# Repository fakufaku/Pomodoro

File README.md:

Pomodoro
========

A custom built timer for the [pomodoro technique](http://pomodorotechnique.com/).

Use it
------

1. One click starts a 25 minutes _work_ counter. Five yellow LED indicates how
  many slices of five minutes are left. There is a discrete beep when the timer
  expires. The LED then flashes to remind you to go into _rest_ mode.
2. A second click starts a 5 minutes _rest_ counter. A **red** LED is turned on.
  There is a discrete beep when it expires. Then the timer turns off.
3. If you wish the turn the timer off during _rest_ mode, click a third time the button.

Build it
--------

### Bill Of Material

* 1x ATtiny85
* 5x LED yellow, SMD 0805
* 1x LED red, SMD 0805
* 3x 22 Ohm Resistor, SMD 0805
* 2x 1K Ohm Resistor, SMD 0805
* 1x NPN BJT transistor, SOT-23 (BC846CMTF)
* 1x 1mH Inductor, SMD 1007
* 1x Buzzer, SMD [mouser](http://www.mouser.com/ProductDetail/Kobitone/254-PB501-ROX/?qs=%2fha2pyFaduio21Wb3%2fEgDw7Itv2u2RCUk%252bCSGDldQmgXvX6wRiKaqw%3d%3d)
* 1x CR2032 coin cell holder, SMD [mouser](http://www.mouser.com/ProductDetail/Linx-Technologies/BAT-HLD-001/?qs=sGAEpiMZZMupuRtfu7GC%252bdEIlVvqTbq%252bJLMEoC1V420%3d)
* 1x Tactile switch, SMD EVQ-Q2 [mouser](http://www.mouser.com/ProductDetail/Panasonic/EVQ-Q2K03W/?qs=sGAEpiMZZMsgGjVA3toVBA4puZS2llK5hCEf4xZ%2f9rI%3d)

### Schematic

### Etch the PCB

The PCB can be etched using the [mask](Pomodoro_mask.eps) provided in EPS format.
Here is a picture of the layout.

### Firmware

The firmware is in the `firmware` folder. It can be uploaded using avrdude and
a [usbtiny-isp](https://www.sparkfun.com/products/9825), for example. The idea is
to press a six-pin header againt the PCB directly when programing. Some spring-loaded
pins would be ideal for the job. The square pad is pad number one of a six-pin ISP
header.

To compile and upload (assuming you have avr-gcc and avrdude installed), type the
following in a terminal.

    make avrdude

The Code
--------

My goal was to use explore the possibilities of the ATtiny85 microcontroller. We use it here
as a timer that first counts 25 minutes (work time) and emit a signal. Then, we can start a second
counter for 5 minutes (rest time). Here is what we use.

* A tactile switch connected to the _INT0_ of the avr as the sole user input. We use it
  to turn the counter off and switch between different modes.
* A buzzer to give a discrete signal when the timer expires. The buzzer is driven
    by _TIMER0_ in PWM mode at 4 kHz, 50% duty cycle.
* As many LEDs as possible to indicate the progress of the timer. By default,
    the ATtiny85 has 5 GPIO pins (we could add an extra one, but would lose ISP).
    We have thus 3 GPIO remaining.   
    We assign all of them to LEDs and using
    [charlieplexing](https://en.wikipedia.org/wiki/Charlieplexing), it is
    possible to drive 6 LEDs using only 3 pins. We choose 5 yellow, for every 5
    minutes slice of the first timer, and a single red one, for the _rest time_
    of the second timer.

The code is completely interrupt driven. _TIMER1_ and its overflow interrupt
are used to keep track of time during each state. The tactile switch triggers
an interrupt to wake up the avr, or switch between states. The [finite state
machine](https://en.wikipedia.org/wiki/Finite-state_machine) looks like this.
Blue arrows are state switching triggered by a push on the button. Red arrows
are switching caused by the timer expiration.

The _main_ states are black circles. The grey circles are the transition states.
It was important to add the `BACKOFF` state to debounce the tactile button because it triggered multiple interrupts.

License
-------

2014 (c) Robin Scheibler aka FakuFaku

    "THE BEER-WARE LICENSE" (Revision 42):
    <fakufaku@gmail.com> wrote this file. As long as you retain this notice you
    can do whatever you want with this stuff. If we meet some day, and you think
    this stuff is worth it, you can buy me a beer in return -- Robin Scheibler

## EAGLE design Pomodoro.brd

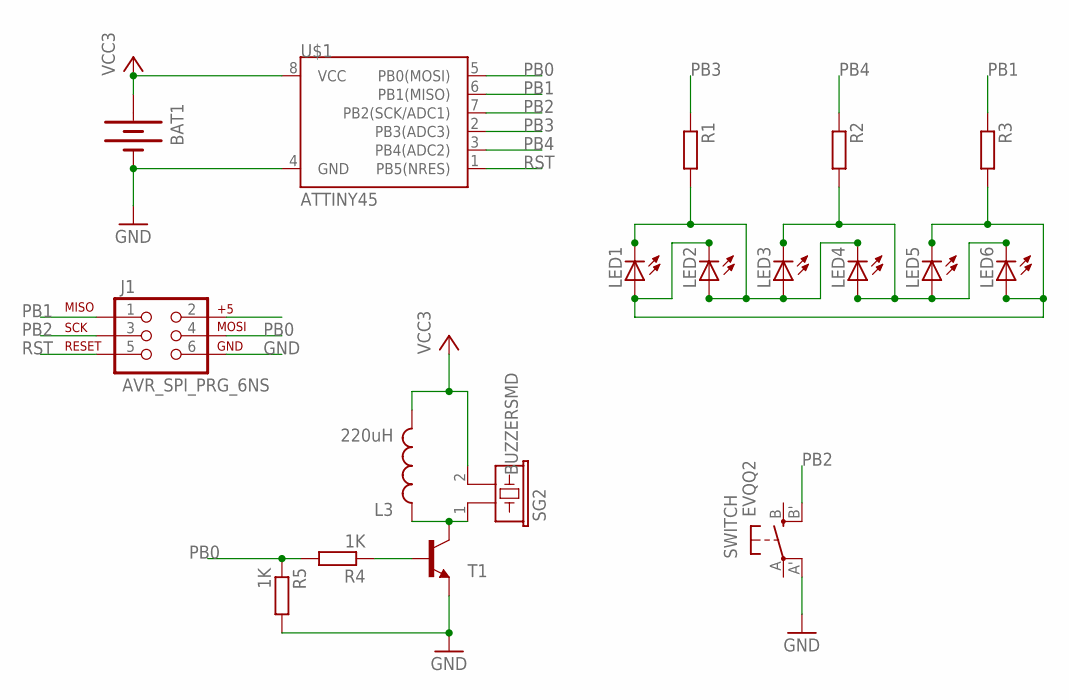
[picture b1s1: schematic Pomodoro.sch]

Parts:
BAT1: BATTERY20SMD; BATTCON_20MM
J1: AVR_SPI_PRG_6NS; 2X3-NS
L3: 220uH; 1007
LED1, LED2, LED3, LED4, LED5, LED6: LEDCHIPLED_0805; CHIPLED_0805
R1, R2, R3: R-EU_R0805; R0805
R4, R5: 1K; R0805
SG2: BUZZERSMD; KOBITONE-254-PB501-ROX
SWITCH: EVQQ2; EVQ-Q2
T1: BC849-NPN-SOT23-BEC; SOT23-BEC
U$1: ATTINY45; SO08-EIAJ

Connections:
GND: BAT1.2 (-), J1.6, R5.2, SWITCH.A' (P1), T1.E, U$1.4 (GND)
unnamed: R4.1, T1.B
unnamed: LED1.C, LED2.A, LED3.A, LED4.C, R1.2
unnamed: L3.1, SG2.1, T1.C
unnamed: LED3.C, LED4.A, LED5.A, LED6.C, R2.2
unnamed: LED1.A, LED2.C, LED5.C, LED6.A, R3.2
PB0: J1.4, R4.2, R5.1, U$1.5 (PB0(MOSI))
PB1: J1.1, R3.1, U$1.6 (PB1(MISO))
PB2: J1.3, SWITCH.B' (S1), U$1.7 (PB2(SCK/ADC1))
PB3: R1.1, U$1.2 (PB3(ADC3))
PB4: R2.1, U$1.3 (PB4(ADC2))
RST: J1.5, U$1.1 (PB5(NRES))
VCC3: BAT1.1 (+), BAT1.3 (+), L3.2, SG2.2, U$1.8 (VCC)

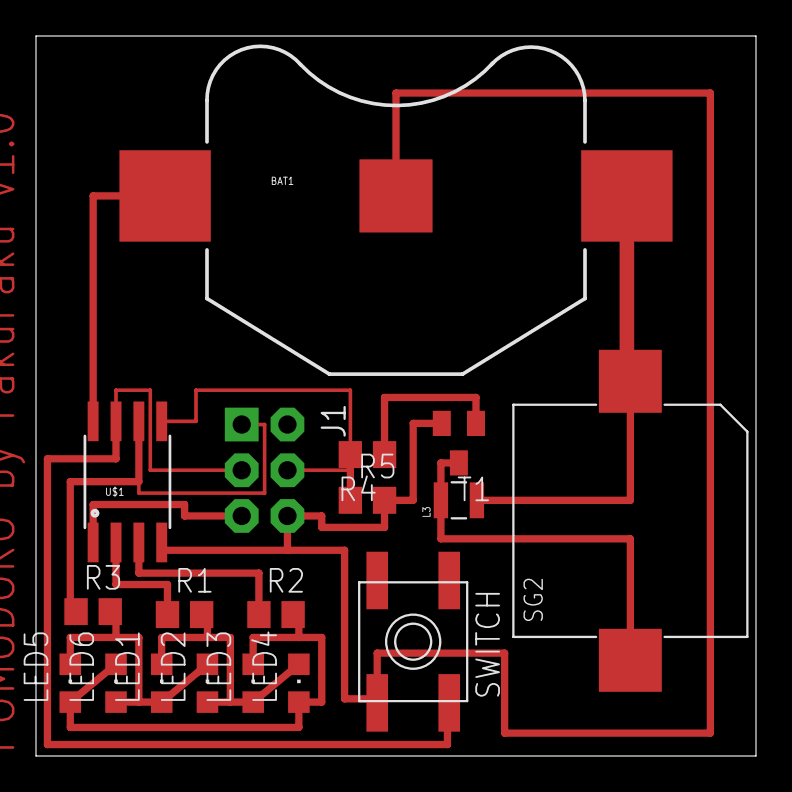
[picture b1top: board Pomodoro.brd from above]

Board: 2 copper layers, 40.0 x 40.0 mm, 18 parts (0 on the bottom side), 13 nets.

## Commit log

2014-01-23 Adding png images of schematics and board. README. gitignore. mask.
2014-01-23 Added license in code.
2014-02-03 Added debounce for tactile switch. Cleaned state machine.
2014-02-03 Added FSM into README.
2014-02-03 Potential bug removed.
2014-02-03 Removed unused variables in main.
2014-02-10 Edit BOM to reflect transistor T1
    According to the datasheet for the BC846CMTF and the schematic,
    In the BOM located in README.md, the line
    1x PNP BPJ transistor, SOT-23 (BC846CMTF)
    should state
    1x NPN BJT transistor, SOT-23 (BC846CMTF)
2014-02-10 section title change in README.
2015-05-24 Modified code to really go into sleep mode.
